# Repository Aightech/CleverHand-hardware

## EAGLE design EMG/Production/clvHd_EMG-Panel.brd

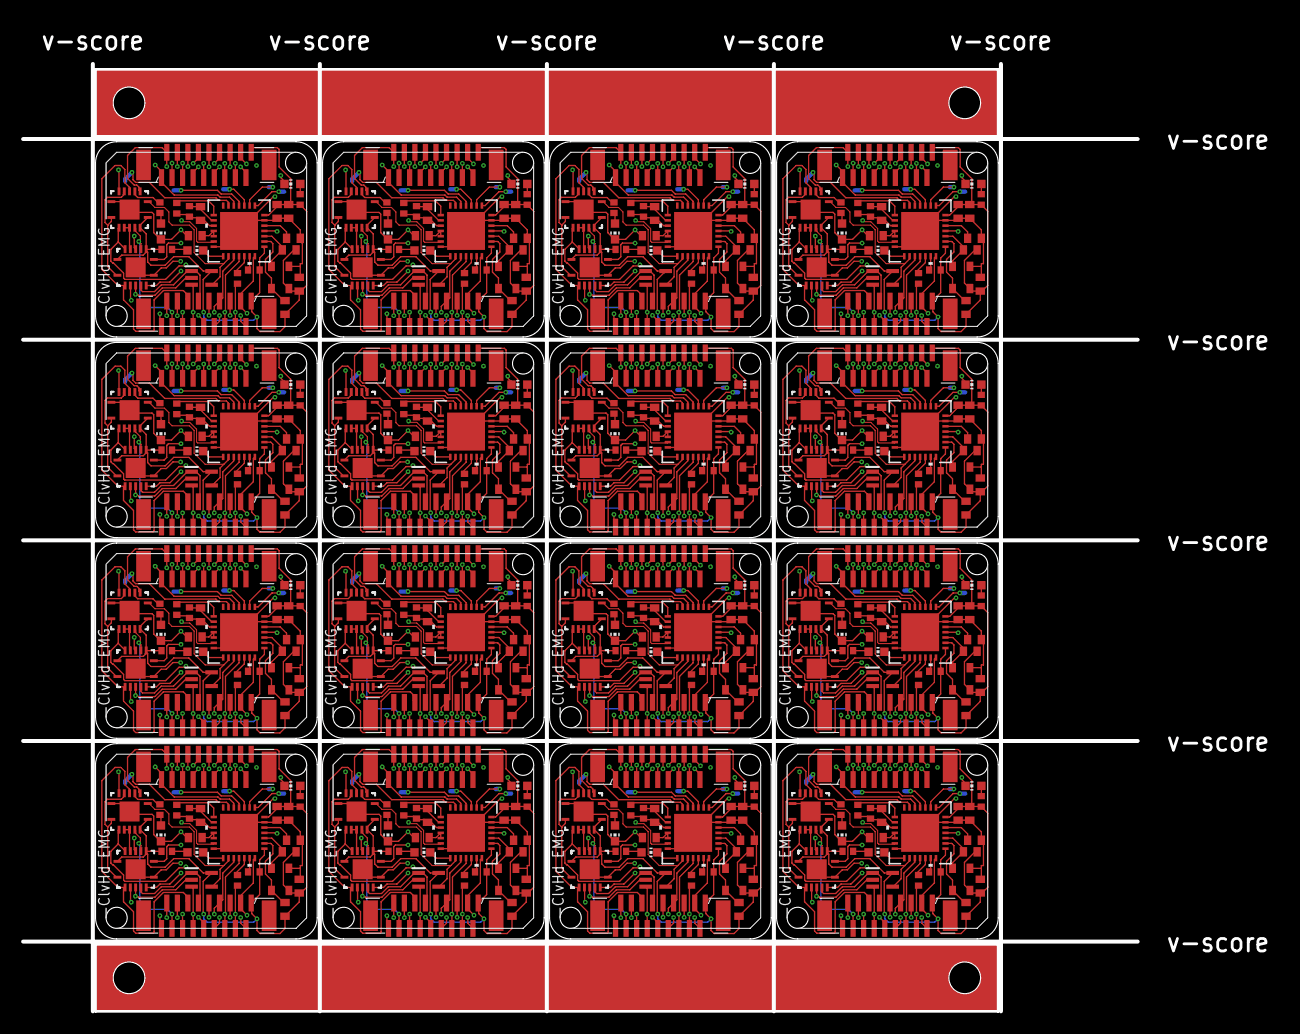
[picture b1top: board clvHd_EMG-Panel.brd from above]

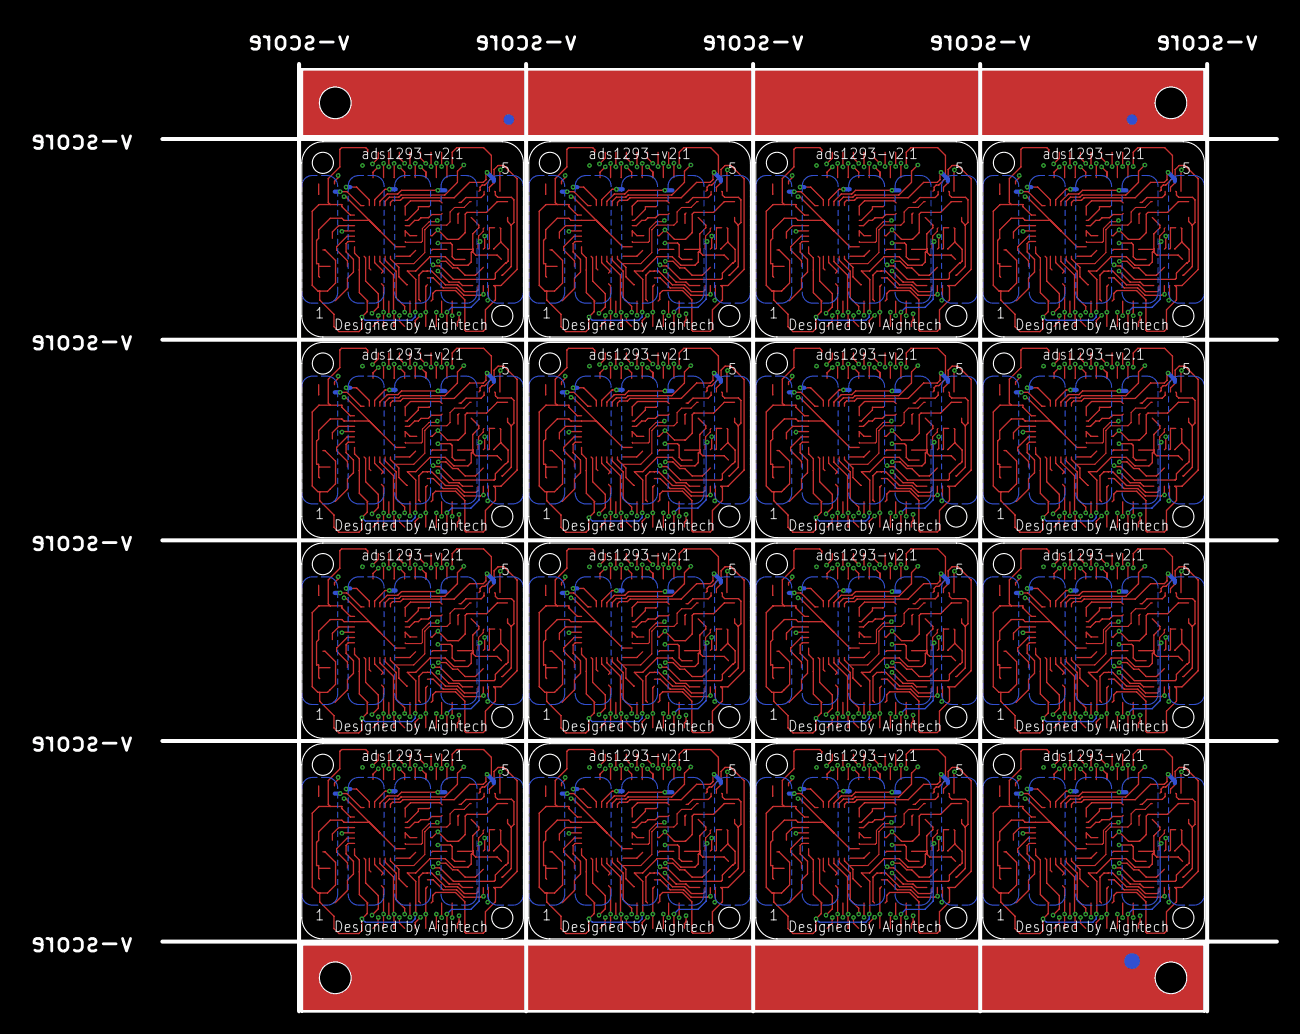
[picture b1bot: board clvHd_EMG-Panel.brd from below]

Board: 4 copper layers, 105.6 x 89.8 mm, 406 parts (3 on the bottom side), 576 nets.

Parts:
AND_IC, AND_IC1, AND_IC2, AND_IC3, AND_IC4, AND_IC5, AND_IC6, AND_IC7, AND_IC8, AND_IC9, AND_IC10, AND_IC11, AND_IC12, AND_IC13, AND_IC14, AND_IC15: SN74ALVC08LARGE; SN74LVC86ARGYR
C1, C2, C9, C10, C14, C15, C25, C26, C33, C34, C41, C42, C49, C50, C57, C58, C65, C66, C73, C74, C81, C82, C89, C90, C97, C98, C105, C106, C113, C114, C121, C122: 22pF; C0402
C3, C4, C6, C7, C12, C13, C16, C17, C18, C19, C22, C23, C27, C28, C30, C31, C35, C36, C38, C39, C43, C44, C46, C47, C51, C52, C54, C55, C59, C60, C62, C63, C67, C68, C70, C71, C75, C76, C78, C79, C83, C84, C86, C87, C91, C92, C94, C95, C99, C100, C102, C103, C107, C108, C110, C111, C115, C116, C118, C119, C123, C124, C126, C127: 100nF; C0402
C5, C11, C21, C29, C37, C45, C53, C61, C69, C77, C85, C93, C101, C109, C117, C125: 1nF; C0402
C8, C20, C24, C32, C40, C48, C56, C64, C72, C80, C88, C96, C104, C112, C120, C128: 1uF; C0402
E$1, E$2, E$3, E$4: FIDUCIAL-1X2
E$5, E$6: FIDUCIAL-1.5X3
J1, J2, J3, J4, J5, J6, J7, J8, J9, J10, J11, J12, J13, J14, J15, J16, J17, J18, J19, J20, J21, J22, J23, J24, J25, J26, J27, J28, J29, J30, J31, J32: XF2J-1824-12
L1, L2, L3, L4, L5, L6, L7, L8, L9, L10, L11, L12, L13, L14, L15, L16, L17, L18, L19, L20, L21, L22, L23, L24, L25, L26, L27, L28, L29, L30, L31, L32, L33, L34, L35, L36, L37, L38, L39, L40, L41, L42, L43, L44, L45, L46, L47, L48: LED 0603; CHIP-LED0603
NAND_IC, NAND_IC1, NAND_IC2, NAND_IC3, NAND_IC4, NAND_IC5, NAND_IC6, NAND_IC7, NAND_IC8, NAND_IC9, NAND_IC10, NAND_IC11, NAND_IC12, NAND_IC13, NAND_IC14, NAND_IC15: SN74LVC1G132DCKT; SOT65P210X110-5N
R1, R3, R7, R8, R9, R12, R16, R20, R21, R23, R27, R28, R30, R34, R35, R37, R41, R42, R44, R48, R49, R51, R55, R56, R58, R62, R63, R65, R69, R70, R72, R76, R77, R79, R83, R84, R86, R90, R91, R93, R97, R98, R100, R104, R105, R107, R111, R112: 100; R0402
R2, R10, R11, R22, R29, R36, R43, R50, R57, R64, R71, R78, R85, R92, R99, R106: 51; R0402
R4, R13, R17, R24, R31, R38, R45, R52, R59, R66, R73, R80, R87, R94, R101, R108: 1M; R0402
R5, R14, R18, R25, R32, R39, R46, R53, R60, R67, R74, R81, R88, R95, R102, R109: 10k; R0402
R6, R15, R19, R26, R33, R40, R47, R54, R61, R68, R75, R82, R89, R96, R103, R110: 10M; R0402
U1, U2, U3, U4, U5, U6, U7, U8, U9, U10, U11, U12, U13, U14, U15, U16: ADS1293CISQ/NOPB; RSG28_3P6X3P6_TEX
U$1, U$2, U$3, U$4, U$5, U$6, U$7, U$8, U$9, U$10, U$11, U$12, U$13, U$14, U$15, U$16: C387328; SMD-3225_4P
XOR_IC, XOR_IC1, XOR_IC2, XOR_IC3, XOR_IC4, XOR_IC5, XOR_IC6, XOR_IC7, XOR_IC8, XOR_IC9, XOR_IC10, XOR_IC11, XOR_IC12, XOR_IC13, XOR_IC14, XOR_IC15: SN74LVC86A; SN74LVC86ARGYR

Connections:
A0: AND_IC.12, J1.16, XOR_IC.10
A1: AND_IC.9, J1.14, XOR_IC.13
A2: AND_IC.4, J1.13, XOR_IC.2
A3: J1.11, NAND_IC.1, XOR_IC.5
A4: AND_IC1.9, J3.14, XOR_IC1.13
A5: AND_IC1.4, J3.13, XOR_IC1.2
A6: J3.11, NAND_IC1.1, XOR_IC1.5
A7: AND_IC1.12, J3.16, XOR_IC1.10
A8: AND_IC2.9, J5.14, XOR_IC2.13
A9: AND_IC2.4, J5.13, XOR_IC2.2
A10: J5.11, NAND_IC2.1, XOR_IC2.5
A11: AND_IC2.12, J5.16, XOR_IC2.10
A12: AND_IC3.9, J7.14, XOR_IC3.13
A13: AND_IC3.4, J7.13, XOR_IC3.2
A14: J7.11, NAND_IC3.1, XOR_IC3.5
A15: AND_IC3.12, J7.16, XOR_IC3.10
A16: AND_IC4.9, J9.14, XOR_IC4.13
A17: AND_IC4.4, J9.13, XOR_IC4.2
A18: J9.11, NAND_IC4.1, XOR_IC4.5
A19: AND_IC4.12, J9.16, XOR_IC4.10
A20: AND_IC5.9, J11.14, XOR_IC5.13
A21: AND_IC5.4, J11.13, XOR_IC5.2
A22: J11.11, NAND_IC5.1, XOR_IC5.5
A23: AND_IC5.12, J11.16, XOR_IC5.10
A24: AND_IC6.9, J13.14, XOR_IC6.13
A25: AND_IC6.4, J13.13, XOR_IC6.2
A26: J13.11, NAND_IC6.1, XOR_IC6.5
A27: AND_IC6.12, J13.16, XOR_IC6.10
A28: AND_IC7.9, J15.14, XOR_IC7.13
A29: AND_IC7.4, J15.13, XOR_IC7.2
A30: J15.11, NAND_IC7.1, XOR_IC7.5
A31: AND_IC7.12, J15.16, XOR_IC7.10
A32: AND_IC8.9, J17.14, XOR_IC8.13
A33: AND_IC8.4, J17.13, XOR_IC8.2
A34: J17.11, NAND_IC8.1, XOR_IC8.5
A35: AND_IC8.12, J17.16, XOR_IC8.10
A36: AND_IC9.9, J19.14, XOR_IC9.13
A37: AND_IC9.4, J19.13, XOR_IC9.2
A38: J19.11, NAND_IC9.1, XOR_IC9.5
A39: AND_IC9.12, J19.16, XOR_IC9.10
A40: AND_IC10.9, J21.14, XOR_IC10.13
A41: AND_IC10.4, J21.13, XOR_IC10.2
A42: J21.11, NAND_IC10.1, XOR_IC10.5
A43: AND_IC10.12, J21.16, XOR_IC10.10
A44: AND_IC11.9, J23.14, XOR_IC11.13
A45: AND_IC11.4, J23.13, XOR_IC11.2
A46: J23.11, NAND_IC11.1, XOR_IC11.5
A47: AND_IC11.12, J23.16, XOR_IC11.10
A48: AND_IC12.9, J25.14, XOR_IC12.13
A49: AND_IC12.4, J25.13, XOR_IC12.2
A50: J25.11, NAND_IC12.1, XOR_IC12.5
A51: AND_IC12.12, J25.16, XOR_IC12.10
A52: AND_IC13.9, J27.14, XOR_IC13.13
A53: AND_IC13.4, J27.13, XOR_IC13.2
A54: J27.11, NAND_IC13.1, XOR_IC13.5
A55: AND_IC13.12, J27.16, XOR_IC13.10
A56: AND_IC14.9, J29.14, XOR_IC14.13
A57: AND_IC14.4, J29.13, XOR_IC14.2
A58: J29.11, NAND_IC14.1, XOR_IC14.5
A59: AND_IC14.12, J29.16, XOR_IC14.10
A60: AND_IC15.9, J31.14, XOR_IC15.13
A61: AND_IC15.4, J31.13, XOR_IC15.2
A62: J31.11, NAND_IC15.1, XOR_IC15.5
A63: AND_IC15.12, J31.16, XOR_IC15.10
ALARMB: L2.C, U1.15
ALARMB1: L4.C, U2.15
ALARMB2: L7.C, U3.15
ALARMB3: L10.C, U4.15
ALARMB4: L13.C, U5.15
ALARMB5: L16.C, U6.15
ALARMB6: L19.C, U7.15
ALARMB7: L22.C, U8.15
ALARMB8: L25.C, U9.15
ALARMB9: L28.C, U10.15
ALARMB10: L31.C, U11.15
ALARMB11: L34.C, U12.15
ALARMB12: L37.C, U13.15
ALARMB13: L40.C, U14.15
ALARMB14: L43.C, U15.15
ALARMB15: L46.C, U16.15
CLK: J1.3, J2.16, U1.21
CLK1: J3.3, J4.16, U2.21
CLK2: J5.3, J6.16, U3.21
CLK3: J7.3, J8.16, U4.21
CLK4: J9.3, J10.16, U5.21
CLK5: J11.3, J12.16, U6.21
CLK6: J13.3, J14.16, U7.21
CLK7: J15.3, J16.16, U8.21
CLK8: J17.3, J18.16, U9.21
CLK9: J19.3, J20.16, U10.21
CLK10: J21.3, J22.16, U11.21
CLK11: J23.3, J24.16, U12.21
CLK12: J25.3, J26.16, U13.21
CLK13: J27.3, J28.16, U14.21
CLK14: J29.3, J30.16, U15.21
CLK15: J31.3, J32.16, U16.21
CMOUT: R14.1, U1.8
CMOUT1: R5.1, U2.8
CMOUT2: R18.1, U3.8
CMOUT3: R25.1, U4.8
CMOUT4: R32.1, U5.8
CMOUT5: R39.1, U6.8
CMOUT6: R46.1, U7.8
CMOUT7: R53.1, U8.8
CMOUT8: R60.1, U9.8
CMOUT9: R67.1, U10.8
CMOUT10: R74.1, U11.8
CMOUT11: R81.1, U12.8
CMOUT12: R88.1, U13.8
CMOUT13: R95.1, U14.8
CMOUT14: R102.1, U15.8
CMOUT15: R109.1, U16.8
CS: AND_IC.1, NAND_IC.4, U1.16
CS1: AND_IC1.1, NAND_IC1.4, U2.16
CS2: AND_IC2.1, NAND_IC2.4, U3.16
CS3: AND_IC3.1, NAND_IC3.4, U4.16
CS4: AND_IC4.1, NAND_IC4.4, U5.16
CS5: AND_IC5.1, NAND_IC5.4, U6.16
CS6: AND_IC6.1, NAND_IC6.4, U7.16
CS7: AND_IC7.1, NAND_IC7.4, U8.16
CS8: AND_IC8.1, NAND_IC8.4, U9.16
CS9: AND_IC9.1, NAND_IC9.4, U10.16
CS10: AND_IC10.1, NAND_IC10.4, U11.16
CS11: AND_IC11.1, NAND_IC11.4, U12.16
CS12: AND_IC12.1, NAND_IC12.4, U13.16
CS13: AND_IC13.1, NAND_IC13.4, U14.16
CS14: AND_IC14.1, NAND_IC14.4, U15.16
CS15: AND_IC15.1, NAND_IC15.4, U16.16
DIN: J1.6, J2.13, U1.18
DIN1: J3.6, J4.13, U2.18
DIN2: J5.6, J6.13, U3.18
DIN3: J7.6, J8.13, U4.18
DIN4: J9.6, J10.13, U5.18
DIN5: J11.6, J12.13, U6.18
DIN6: J13.6, J14.13, U7.18
DIN7: J15.6, J16.13, U8.18
DIN8: J17.6, J18.13, U9.18
DIN9: J19.6, J20.13, U10.18
DIN10: J21.6, J22.13, U11.18
DIN11: J23.6, J24.13, U12.18
DIN12: J25.6, J26.13, U13.18
DIN13: J27.6, J28.13, U14.18
DIN14: J29.6, J30.13, U15.18
DIN15: J31.6, J32.13, U16.18
DOUT: J1.4, J2.15, R10.2
DOUT1: J3.4, J4.15, R2.2
DOUT2: J5.4, J6.15, R11.2
DOUT3: J7.4, J8.15, R22.2
DOUT4: J9.4, J10.15, R29.2
DOUT5: J11.4, J12.15, R36.2
DOUT6: J13.4, J14.15, R43.2
DOUT7: J15.4, J16.15, R50.2
DOUT8: J17.4, J18.15, R57.2
DOUT9: J19.4, J20.15, R64.2
DOUT10: J21.4, J22.15, R71.2
DOUT11: J23.4, J24.15, R78.2
DOUT12: J25.4, J26.15, R85.2
DOUT13: J27.4, J28.15, R92.2
DOUT14: J29.4, J30.15, R99.2
DOUT15: J31.4, J32.15, R106.2
DRDYB: R13.1, U1.20
DRDYB1: R4.1, U2.20
DRDYB2: R17.1, U3.20
DRDYB3: R24.1, U4.20
DRDYB4: R31.1, U5.20
DRDYB5: R38.1, U6.20
DRDYB6: R45.1, U7.20
DRDYB7: R52.1, U8.20
DRDYB8: R59.1, U9.20
DRDYB9: R66.1, U10.20
DRDYB10: R73.1, U11.20
DRDYB11: R80.1, U12.20
DRDYB12: R87.1, U13.20
DRDYB13: R94.1, U14.20
DRDYB14: R101.1, U15.20
DRDYB15: R108.1, U16.20
GND: AND_IC.7, AND_IC.15, C12.2, C13.2, C16.2, C19.2, C20.2, J1.2, J1.5, J1.8, J1.12, J1.15, J2.4, J2.7, J2.11, J2.14, J2.17, L1.C, L3.C, NAND_IC.3, U1.14, U1.27, U1.29, U$1.2, XOR_IC.7, XOR_IC.15
GND1: AND_IC1.7, AND_IC1.15, C3.2, C4.2, C6.2, C7.2, C8.2, J3.2, J3.5, J3.8, J3.12, J3.15, J4.4, J4.7, J4.11, J4.14, J4.17, L5.C, L6.C, NAND_IC1.3, U2.14, U2.27, U2.29, U$2.2, XOR_IC1.7, XOR_IC1.15
GND2: AND_IC2.7, AND_IC2.15, C17.2, C18.2, C22.2, C23.2, C24.2, J5.2, J5.5, J5.8, J5.12, J5.15, J6.4, J6.7, J6.11, J6.14, J6.17, L8.C, L9.C, NAND_IC2.3, U3.14, U3.27, U3.29, U$3.2, XOR_IC2.7, XOR_IC2.15
GND3: AND_IC3.7, AND_IC3.15, C27.2, C28.2, C30.2, C31.2, C32.2, J7.2, J7.5, J7.8, J7.12, J7.15, J8.4, J8.7, J8.11, J8.14, J8.17, L11.C, L12.C, NAND_IC3.3, U4.14, U4.27, U4.29, U$4.2, XOR_IC3.7, XOR_IC3.15
GND4: AND_IC4.7, AND_IC4.15, C35.2, C36.2, C38.2, C39.2, C40.2, J9.2, J9.5, J9.8, J9.12, J9.15, J10.4, J10.7, J10.11, J10.14, J10.17, L14.C, L15.C, NAND_IC4.3, U5.14, U5.27, U5.29, U$5.2, XOR_IC4.7, XOR_IC4.15
GND5: AND_IC5.7, AND_IC5.15, C43.2, C44.2, C46.2, C47.2, C48.2, J11.2, J11.5, J11.8, J11.12, J11.15, J12.4, J12.7, J12.11, J12.14, J12.17, L17.C, L18.C, NAND_IC5.3, U6.14, U6.27, U6.29, U$6.2, XOR_IC5.7, XOR_IC5.15
GND6: AND_IC6.7, AND_IC6.15, C51.2, C52.2, C54.2, C55.2, C56.2, J13.2, J13.5, J13.8, J13.12, J13.15, J14.4, J14.7, J14.11, J14.14, J14.17, L20.C, L21.C, NAND_IC6.3, U7.14, U7.27, U7.29, U$7.2, XOR_IC6.7, XOR_IC6.15
GND7: AND_IC7.7, AND_IC7.15, C59.2, C60.2, C62.2, C63.2, C64.2, J15.2, J15.5, J15.8, J15.12, J15.15, J16.4, J16.7, J16.11, J16.14, J16.17, L23.C, L24.C, NAND_IC7.3, U8.14, U8.27, U8.29, U$8.2, XOR_IC7.7, XOR_IC7.15
GND8: AND_IC8.7, AND_IC8.15, C67.2, C68.2, C70.2, C71.2, C72.2, J17.2, J17.5, J17.8, J17.12, J17.15, J18.4, J18.7, J18.11, J18.14, J18.17, L26.C, L27.C, NAND_IC8.3, U9.14, U9.27, U9.29, U$9.2, XOR_IC8.7, XOR_IC8.15
GND9: AND_IC9.7, AND_IC9.15, C75.2, C76.2, C78.2, C79.2, C80.2, J19.2, J19.5, J19.8, J19.12, J19.15, J20.4, J20.7, J20.11, J20.14, J20.17, L29.C, L30.C, NAND_IC9.3, U10.14, U10.27, U10.29, U$10.2, XOR_IC9.7, XOR_IC9.15
GND10: AND_IC10.7, AND_IC10.15, C83.2, C84.2, C86.2, C87.2, C88.2, J21.2, J21.5, J21.8, J21.12, J21.15, J22.4, J22.7, J22.11, J22.14, J22.17, L32.C, L33.C, NAND_IC10.3, U11.14, U11.27, U11.29, U$11.2, XOR_IC10.7, XOR_IC10.15
GND11: AND_IC11.7, AND_IC11.15, C91.2, C92.2, C94.2, C95.2, C96.2, J23.2, J23.5, J23.8, J23.12, J23.15, J24.4, J24.7, J24.11, J24.14, J24.17, L35.C, L36.C, NAND_IC11.3, U12.14, U12.27, U12.29, U$12.2, XOR_IC11.7, XOR_IC11.15
GND12: AND_IC12.7, AND_IC12.15, C99.2, C100.2, C102.2, C103.2, C104.2, J25.2, J25.5, J25.8, J25.12, J25.15, J26.4, J26.7, J26.11, J26.14, J26.17, L38.C, L39.C, NAND_IC12.3, U13.14, U13.27, U13.29, U$13.2, XOR_IC12.7, XOR_IC12.15
GND13: AND_IC13.7, AND_IC13.15, C107.2, C108.2, C110.2, C111.2, C112.2, J27.2, J27.5, J27.8, J27.12, J27.15, J28.4, J28.7, J28.11, J28.14, J28.17, L41.C, L42.C, NAND_IC13.3, U14.14, U14.27, U14.29, U$14.2, XOR_IC13.7, XOR_IC13.15
GND14: AND_IC14.7, AND_IC14.15, C115.2, C116.2, C118.2, C119.2, C120.2, J29.2, J29.5, J29.8, J29.12, J29.15, J30.4, J30.7, J30.11, J30.14, J30.17, L44.C, L45.C, NAND_IC14.3, U15.14, U15.27, U15.29, U$15.2, XOR_IC14.7, XOR_IC14.15
GND15: AND_IC15.7, AND_IC15.15, C123.2, C124.2, C126.2, C127.2, C128.2, J31.2, J31.5, J31.8, J31.12, J31.15, J32.4, J32.7, J32.11, J32.14, J32.17, L47.C, L48.C, NAND_IC15.3, U16.14, U16.27, U16.29, U$16.2, XOR_IC15.7, XOR_IC15.15
GPIO1: AND_IC.2, J1.17, J2.2
GPIO2: AND_IC1.2, J3.17, J4.2
GPIO3: AND_IC2.2, J5.17, J6.2
GPIO4: AND_IC3.2, J7.17, J8.2
GPIO5: AND_IC4.2, J9.17, J10.2
GPIO6: AND_IC5.2, J11.17, J12.2
GPIO7: AND_IC6.2, J13.17, J14.2
GPIO8: AND_IC7.2, J15.17, J16.2
GPIO9: AND_IC8.2, J17.17, J18.2
GPIO10: AND_IC9.2, J19.17, J20.2
GPIO11: AND_IC10.2, J21.17, J22.2
GPIO12: AND_IC11.2, J23.17, J24.2
GPIO13: AND_IC12.2, J25.17, J26.2
GPIO14: AND_IC13.2, J27.17, J28.2
GPIO15: AND_IC14.2, J29.17, J30.2
GPIO16: AND_IC15.2, J31.17, J32.2
IN5: J1.18, J2.1, U1.5
IN10: J3.18, J4.1, U2.5
IN16: J5.18, J6.1, U3.5
IN22: J7.18, J8.1, U4.5
IN28: J9.18, J10.1, U5.5
IN34: J11.18, J12.1, U6.5
IN40: J13.18, J14.1, U7.5
IN46: J15.18, J16.1, U8.5
IN52: J17.18, J18.1, U9.5
IN58: J19.18, J20.1, U10.5
IN64: J21.18, J22.1, U11.5
IN70: J23.18, J24.1, U12.5
IN76: J25.18, J26.1, U13.5
IN82: J27.18, J28.1, U14.5
IN88: J29.18, J30.1, U15.5
IN94: J31.18, J32.1, U16.5
unnamed: R2.1, U2.19
unnamed: L1.A, R7.2
unnamed: R10.1, U1.19
unnamed: C10.2, U1.23, U$1.4
unnamed: AND_IC.3, R1.2
unnamed: L2.A, R12.1
unnamed: L3.A, R1.1
unnamed: C9.2, U1.24, U$1.3
unnamed: C20.1, U1.26
unnamed: C2.2, U2.23, U$2.4
unnamed: AND_IC.10, AND_IC.11, XOR_IC.12
unnamed: C1.2, U2.24, U$2.3
unnamed: AND_IC.5, AND_IC.8, XOR_IC.1
unnamed: C5.1, R5.2, R6.2, U2.10
unnamed: C11.1, R14.2, R15.2, U1.10
unnamed: AND_IC.6, NAND_IC.2, XOR_IC.4
unnamed: C8.1, U2.26
unnamed: L5.A, R8.2
unnamed: L4.A, R3.1
unnamed: AND_IC1.3, R9.2
unnamed: L6.A, R9.1
unnamed: AND_IC1.6, NAND_IC1.2, XOR_IC1.4
unnamed: AND_IC1.5, AND_IC1.8, XOR_IC1.1
unnamed: AND_IC1.10, AND_IC1.11, XOR_IC1.12
unnamed: R11.1, U3.19
unnamed: C15.2, U3.23, U$3.4
unnamed: C14.2, U3.24, U$3.3
unnamed: C21.1, R18.2, R19.2, U3.10
unnamed: C24.1, U3.26
unnamed: L8.A, R20.2
unnamed: L7.A, R16.1
unnamed: AND_IC2.3, R21.2
unnamed: L9.A, R21.1
unnamed: AND_IC2.6, NAND_IC2.2, XOR_IC2.4
unnamed: AND_IC2.5, AND_IC2.8, XOR_IC2.1
unnamed: AND_IC2.10, AND_IC2.11, XOR_IC2.12
unnamed: R22.1, U4.19
unnamed: C26.2, U4.23, U$4.4
unnamed: C25.2, U4.24, U$4.3
unnamed: C29.1, R25.2, R26.2, U4.10
unnamed: C32.1, U4.26
unnamed: L11.A, R27.2
unnamed: L10.A, R23.1
unnamed: AND_IC3.3, R28.2
unnamed: L12.A, R28.1
unnamed: AND_IC3.6, NAND_IC3.2, XOR_IC3.4
unnamed: AND_IC3.5, AND_IC3.8, XOR_IC3.1
unnamed: AND_IC3.10, AND_IC3.11, XOR_IC3.12
unnamed: R29.1, U5.19
unnamed: C34.2, U5.23, U$5.4
unnamed: C33.2, U5.24, U$5.3
unnamed: C37.1, R32.2, R33.2, U5.10
unnamed: C40.1, U5.26
unnamed: L14.A, R34.2
unnamed: L13.A, R30.1
unnamed: AND_IC4.3, R35.2
unnamed: L15.A, R35.1
unnamed: AND_IC4.6, NAND_IC4.2, XOR_IC4.4
unnamed: AND_IC4.5, AND_IC4.8, XOR_IC4.1
unnamed: AND_IC4.10, AND_IC4.11, XOR_IC4.12
unnamed: R36.1, U6.19
unnamed: C42.2, U6.23, U$6.4
unnamed: C41.2, U6.24, U$6.3
unnamed: C45.1, R39.2, R40.2, U6.10
unnamed: C48.1, U6.26
unnamed: L17.A, R41.2
unnamed: L16.A, R37.1
unnamed: AND_IC5.3, R42.2
unnamed: L18.A, R42.1
unnamed: AND_IC5.6, NAND_IC5.2, XOR_IC5.4
unnamed: AND_IC5.5, AND_IC5.8, XOR_IC5.1
unnamed: AND_IC5.10, AND_IC5.11, XOR_IC5.12
unnamed: R43.1, U7.19
unnamed: C50.2, U7.23, U$7.4
unnamed: C49.2, U7.24, U$7.3
unnamed: C53.1, R46.2, R47.2, U7.10
unnamed: C56.1, U7.26
unnamed: L20.A, R48.2
unnamed: L19.A, R44.1
unnamed: AND_IC6.3, R49.2
unnamed: L21.A, R49.1
unnamed: AND_IC6.6, NAND_IC6.2, XOR_IC6.4
unnamed: AND_IC6.5, AND_IC6.8, XOR_IC6.1
unnamed: AND_IC6.10, AND_IC6.11, XOR_IC6.12
unnamed: R50.1, U8.19
unnamed: C58.2, U8.23, U$8.4
unnamed: C57.2, U8.24, U$8.3
unnamed: C61.1, R53.2, R54.2, U8.10
unnamed: C64.1, U8.26
unnamed: L23.A, R55.2
unnamed: L22.A, R51.1
unnamed: AND_IC7.3, R56.2
unnamed: L24.A, R56.1
unnamed: AND_IC7.6, NAND_IC7.2, XOR_IC7.4
unnamed: AND_IC7.5, AND_IC7.8, XOR_IC7.1
unnamed: AND_IC7.10, AND_IC7.11, XOR_IC7.12
unnamed: R57.1, U9.19
unnamed: C66.2, U9.23, U$9.4
unnamed: C65.2, U9.24, U$9.3
unnamed: C69.1, R60.2, R61.2, U9.10
unnamed: C72.1, U9.26
unnamed: L26.A, R62.2
unnamed: L25.A, R58.1
unnamed: AND_IC8.3, R63.2
unnamed: L27.A, R63.1
unnamed: AND_IC8.6, NAND_IC8.2, XOR_IC8.4
unnamed: AND_IC8.5, AND_IC8.8, XOR_IC8.1
unnamed: AND_IC8.10, AND_IC8.11, XOR_IC8.12
unnamed: R64.1, U10.19
unnamed: C74.2, U10.23, U$10.4
unnamed: C73.2, U10.24, U$10.3
unnamed: C77.1, R67.2, R68.2, U10.10
unnamed: C80.1, U10.26
unnamed: L29.A, R69.2
unnamed: L28.A, R65.1
unnamed: AND_IC9.3, R70.2
unnamed: L30.A, R70.1
unnamed: AND_IC9.6, NAND_IC9.2, XOR_IC9.4
unnamed: AND_IC9.5, AND_IC9.8, XOR_IC9.1
unnamed: AND_IC9.10, AND_IC9.11, XOR_IC9.12
unnamed: R71.1, U11.19
unnamed: C82.2, U11.23, U$11.4
unnamed: C81.2, U11.24, U$11.3
unnamed: C85.1, R74.2, R75.2, U11.10
unnamed: C88.1, U11.26
unnamed: L32.A, R76.2
unnamed: L31.A, R72.1
unnamed: AND_IC10.3, R77.2
unnamed: L33.A, R77.1
unnamed: AND_IC10.6, NAND_IC10.2, XOR_IC10.4
unnamed: AND_IC10.5, AND_IC10.8, XOR_IC10.1
unnamed: AND_IC10.10, AND_IC10.11, XOR_IC10.12
unnamed: R78.1, U12.19
unnamed: C90.2, U12.23, U$12.4
unnamed: C89.2, U12.24, U$12.3
unnamed: C93.1, R81.2, R82.2, U12.10
unnamed: C96.1, U12.26
unnamed: L35.A, R83.2
unnamed: L34.A, R79.1
unnamed: AND_IC11.3, R84.2
unnamed: L36.A, R84.1
unnamed: AND_IC11.6, NAND_IC11.2, XOR_IC11.4
unnamed: AND_IC11.5, AND_IC11.8, XOR_IC11.1
unnamed: AND_IC11.10, AND_IC11.11, XOR_IC11.12
unnamed: R85.1, U13.19
unnamed: C98.2, U13.23, U$13.4
unnamed: C97.2, U13.24, U$13.3
unnamed: C101.1, R88.2, R89.2, U13.10
unnamed: C104.1, U13.26
unnamed: L38.A, R90.2
unnamed: L37.A, R86.1
unnamed: AND_IC12.3, R91.2
unnamed: L39.A, R91.1
unnamed: AND_IC12.6, NAND_IC12.2, XOR_IC12.4
unnamed: AND_IC12.5, AND_IC12.8, XOR_IC12.1
unnamed: AND_IC12.10, AND_IC12.11, XOR_IC12.12
unnamed: R92.1, U14.19
unnamed: C106.2, U14.23, U$14.4
unnamed: C105.2, U14.24, U$14.3
unnamed: C109.1, R95.2, R96.2, U14.10
unnamed: C112.1, U14.26
unnamed: L41.A, R97.2
unnamed: L40.A, R93.1
unnamed: AND_IC13.3, R98.2
unnamed: L42.A, R98.1
unnamed: AND_IC13.6, NAND_IC13.2, XOR_IC13.4
unnamed: AND_IC13.5, AND_IC13.8, XOR_IC13.1
unnamed: AND_IC13.10, AND_IC13.11, XOR_IC13.12
unnamed: R99.1, U15.19
unnamed: C114.2, U15.23, U$15.4
unnamed: C113.2, U15.24, U$15.3
unnamed: C117.1, R102.2, R103.2, U15.10
unnamed: C120.1, U15.26
unnamed: L44.A, R104.2
unnamed: L43.A, R100.1
unnamed: AND_IC14.3, R105.2
unnamed: L45.A, R105.1
unnamed: AND_IC14.6, NAND_IC14.2, XOR_IC14.4
unnamed: AND_IC14.5, AND_IC14.8, XOR_IC14.1
unnamed: AND_IC14.10, AND_IC14.11, XOR_IC14.12
unnamed: R106.1, U16.19
unnamed: C122.2, U16.23, U$16.4
unnamed: C121.2, U16.24, U$16.3
unnamed: C125.1, R109.2, R110.2, U16.10
unnamed: C128.1, U16.26
unnamed: L47.A, R111.2
unnamed: L46.A, R107.1
unnamed: AND_IC15.3, R112.2
unnamed: L48.A, R112.1
unnamed: AND_IC15.6, NAND_IC15.2, XOR_IC15.4
unnamed: AND_IC15.5, AND_IC15.8, XOR_IC15.1
unnamed: AND_IC15.10, AND_IC15.11, XOR_IC15.12
RLDOUT: C11.2, R15.1, U1.9
RLDOUT1: C5.2, R6.1, U2.9
RLDOUT2: C21.2, R19.1, U3.9
RLDOUT3: C29.2, R26.1, U4.9
RLDOUT4: C37.2, R33.1, U5.9
RLDOUT5: C45.2, R40.1, U6.9
RLDOUT6: C53.2, R47.1, U7.9
RLDOUT7: C61.2, R54.1, U8.9
RLDOUT8: C69.2, R61.1, U9.9
RLDOUT9: C77.2, R68.1, U10.9
RLDOUT10: C85.2, R75.1, U11.9
RLDOUT11: C93.2, R82.1, U12.9
RLDOUT12: C101.2, R89.1, U13.9
RLDOUT13: C109.2, R96.1, U14.9
RLDOUT14: C117.2, R103.1, U15.9
RLDOUT15: C125.2, R110.1, U16.9
RLDREF: C12.1, U1.11, U1.12
RLDREF1: C3.1, U2.11, U2.12
RLDREF2: C17.1, U3.11, U3.12
RLDREF3: C27.1, U4.11, U4.12
RLDREF4: C35.1, U5.11, U5.12
RLDREF5: C43.1, U6.11, U6.12
RLDREF6: C51.1, U7.11, U7.12
RLDREF7: C59.1, U8.11, U8.12
RLDREF8: C67.1, U9.11, U9.12
RLDREF9: C75.1, U10.11, U10.12
RLDREF10: C83.1, U11.11, U11.12
RLDREF11: C91.1, U12.11, U12.12
RLDREF12: C99.1, U13.11, U13.12
RLDREF13: C107.1, U14.11, U14.12
RLDREF14: C115.1, U15.11, U15.12
RLDREF15: C123.1, U16.11, U16.12
RST: J1.10, J2.9, U1.25
RST1: J3.10, J4.9, U2.25
RST2: J5.10, J6.9, U3.25
RST3: J7.10, J8.9, U4.25
RST4: J9.10, J10.9, U5.25
RST5: J11.10, J12.9, U6.25
RST6: J13.10, J14.9, U7.25
RST7: J15.10, J16.9, U8.25
RST8: J17.10, J18.9, U9.25
RST9: J19.10, J20.9, U10.25
RST10: J21.10, J22.9, U11.25
RST11: J23.10, J24.9, U12.25
RST12: J25.10, J26.9, U13.25
RST13: J27.10, J28.9, U14.25
RST14: J29.10, J30.9, U15.25
RST15: J31.10, J32.9, U16.25
S0: J2.3, XOR_IC.8
S1: J2.5, XOR_IC.11
S2: J2.6, XOR_IC.3
S3: J2.8, XOR_IC.6
S4: J4.3, XOR_IC1.8
S5: J4.5, XOR_IC1.11
S6: J4.6, XOR_IC1.3
S7: J4.8, XOR_IC1.6
S8: J6.3, XOR_IC2.8
S9: J6.5, XOR_IC2.11
S10: J6.6, XOR_IC2.3
S11: J6.8, XOR_IC2.6
S12: J8.3, XOR_IC3.8
S13: J8.5, XOR_IC3.11
S14: J8.6, XOR_IC3.3
S15: J8.8, XOR_IC3.6
S16: J10.3, XOR_IC4.8
S17: J10.5, XOR_IC4.11
S18: J10.6, XOR_IC4.3
S19: J10.8, XOR_IC4.6
S20: J12.3, XOR_IC5.8
S21: J12.5, XOR_IC5.11
S22: J12.6, XOR_IC5.3
S23: J12.8, XOR_IC5.6
S24: J14.3, XOR_IC6.8
S25: J14.5, XOR_IC6.11
S26: J14.6, XOR_IC6.3
S27: J14.8, XOR_IC6.6
S28: J16.3, XOR_IC7.8
S29: J16.5, XOR_IC7.11
S30: J16.6, XOR_IC7.3
S31: J16.8, XOR_IC7.6
S32: J18.3, XOR_IC8.8
S33: J18.5, XOR_IC8.11
S34: J18.6, XOR_IC8.3
S35: J18.8, XOR_IC8.6
S36: J20.3, XOR_IC9.8
S37: J20.5, XOR_IC9.11
S38: J20.6, XOR_IC9.3
S39: J20.8, XOR_IC9.6
S40: J22.3, XOR_IC10.8
S41: J22.5, XOR_IC10.11
S42: J22.6, XOR_IC10.3
S43: J22.8, XOR_IC10.6
S44: J24.3, XOR_IC11.8
S45: J24.5, XOR_IC11.11
S46: J24.6, XOR_IC11.3
S47: J24.8, XOR_IC11.6
S48: J26.3, XOR_IC12.8
S49: J26.5, XOR_IC12.11
S50: J26.6, XOR_IC12.3
S51: J26.8, XOR_IC12.6
S52: J28.3, XOR_IC13.8
S53: J28.5, XOR_IC13.11
S54: J28.6, XOR_IC13.3
S55: J28.8, XOR_IC13.6
S56: J30.3, XOR_IC14.8
S57: J30.5, XOR_IC14.11
S58: J30.6, XOR_IC14.3
S59: J30.8, XOR_IC14.6
S60: J32.3, XOR_IC15.8
S61: J32.5, XOR_IC15.11
S62: J32.6, XOR_IC15.3
S63: J32.8, XOR_IC15.6
SCLK: J1.7, J2.12, U1.17
SCLK1: J3.7, J4.12, U2.17
SCLK2: J5.7, J6.12, U3.17
SCLK3: J7.7, J8.12, U4.17
SCLK4: J9.7, J10.12, U5.17
SCLK5: J11.7, J12.12, U6.17
SCLK6: J13.7, J14.12, U7.17
SCLK7: J15.7, J16.12, U8.17
SCLK8: J17.7, J18.12, U9.17
SCLK9: J19.7, J20.12, U10.17
SCLK10: J21.7, J22.12, U11.17
SCLK11: J23.7, J24.12, U12.17
SCLK12: J25.7, J26.12, U13.17
SCLK13: J27.7, J28.12, U14.17
SCLK14: J29.7, J30.12, U15.17
SCLK15: J31.7, J32.12, U16.17
SYNCB: J1.9, J2.10, U1.13
SYNCB1: J3.9, J4.10, U2.13
SYNCB2: J5.9, J6.10, U3.13
SYNCB3: J7.9, J8.10, U4.13
SYNCB4: J9.9, J10.10, U5.13
SYNCB5: J11.9, J12.10, U6.13
SYNCB6: J13.9, J14.10, U7.13
SYNCB7: J15.9, J16.10, U8.13
SYNCB8: J17.9, J18.10, U9.13
SYNCB9: J19.9, J20.10, U10.13
SYNCB10: J21.9, J22.10, U11.13
SYNCB11: J23.9, J24.10, U12.13
SYNCB12: J25.9, J26.10, U13.13
SYNCB13: J27.9, J28.10, U14.13
SYNCB14: J29.9, J30.10, U15.13
SYNCB15: J31.9, J32.10, U16.13
VDD: AND_IC.13, AND_IC.14, C9.1, C10.1, C13.1, C16.1, C19.1, J1.1, J2.18, NAND_IC.5, R7.1, R12.2, R13.2, U1.22, U1.28, U$1.1, XOR_IC.9, XOR_IC.14
VDD1: AND_IC1.13, AND_IC1.14, C1.1, C2.1, C4.1, C6.1, C7.1, J3.1, J4.18, NAND_IC1.5, R3.2, R4.2, R8.1, U2.22, U2.28, U$2.1, XOR_IC1.9, XOR_IC1.14
VDD2: AND_IC2.13, AND_IC2.14, C14.1, C15.1, C18.1, C22.1, C23.1, J5.1, J6.18, NAND_IC2.5, R16.2, R17.2, R20.1, U3.22, U3.28, U$3.1, XOR_IC2.9, XOR_IC2.14
VDD3: AND_IC3.13, AND_IC3.14, C25.1, C26.1, C28.1, C30.1, C31.1, J7.1, J8.18, NAND_IC3.5, R23.2, R24.2, R27.1, U4.22, U4.28, U$4.1, XOR_IC3.9, XOR_IC3.14
VDD4: AND_IC4.13, AND_IC4.14, C33.1, C34.1, C36.1, C38.1, C39.1, J9.1, J10.18, NAND_IC4.5, R30.2, R31.2, R34.1, U5.22, U5.28, U$5.1, XOR_IC4.9, XOR_IC4.14
VDD5: AND_IC5.13, AND_IC5.14, C41.1, C42.1, C44.1, C46.1, C47.1, J11.1, J12.18, NAND_IC5.5, R37.2, R38.2, R41.1, U6.22, U6.28, U$6.1, XOR_IC5.9, XOR_IC5.14
VDD6: AND_IC6.13, AND_IC6.14, C49.1, C50.1, C52.1, C54.1, C55.1, J13.1, J14.18, NAND_IC6.5, R44.2, R45.2, R48.1, U7.22, U7.28, U$7.1, XOR_IC6.9, XOR_IC6.14
VDD7: AND_IC7.13, AND_IC7.14, C57.1, C58.1, C60.1, C62.1, C63.1, J15.1, J16.18, NAND_IC7.5, R51.2, R52.2, R55.1, U8.22, U8.28, U$8.1, XOR_IC7.9, XOR_IC7.14
VDD8: AND_IC8.13, AND_IC8.14, C65.1, C66.1, C68.1, C70.1, C71.1, J17.1, J18.18, NAND_IC8.5, R58.2, R59.2, R62.1, U9.22, U9.28, U$9.1, XOR_IC8.9, XOR_IC8.14
VDD9: AND_IC9.13, AND_IC9.14, C73.1, C74.1, C76.1, C78.1, C79.1, J19.1, J20.18, NAND_IC9.5, R65.2, R66.2, R69.1, U10.22, U10.28, U$10.1, XOR_IC9.9, XOR_IC9.14
VDD10: AND_IC10.13, AND_IC10.14, C81.1, C82.1, C84.1, C86.1, C87.1, J21.1, J22.18, NAND_IC10.5, R72.2, R73.2, R76.1, U11.22, U11.28, U$11.1, XOR_IC10.9, XOR_IC10.14
VDD11: AND_IC11.13, AND_IC11.14, C89.1, C90.1, C92.1, C94.1, C95.1, J23.1, J24.18, NAND_IC11.5, R79.2, R80.2, R83.1, U12.22, U12.28, U$12.1, XOR_IC11.9, XOR_IC11.14
VDD12: AND_IC12.13, AND_IC12.14, C97.1, C98.1, C100.1, C102.1, C103.1, J25.1, J26.18, NAND_IC12.5, R86.2, R87.2, R90.1, U13.22, U13.28, U$13.1, XOR_IC12.9, XOR_IC12.14
VDD13: AND_IC13.13, AND_IC13.14, C105.1, C106.1, C108.1, C110.1, C111.1, J27.1, J28.18, NAND_IC13.5, R93.2, R94.2, R97.1, U14.22, U14.28, U$14.1, XOR_IC13.9, XOR_IC13.14
VDD14: AND_IC14.13, AND_IC14.14, C113.1, C114.1, C116.1, C118.1, C119.1, J29.1, J30.18, NAND_IC14.5, R100.2, R101.2, R104.1, U15.22, U15.28, U$15.1, XOR_IC14.9, XOR_IC14.14
VDD15: AND_IC15.13, AND_IC15.14, C121.1, C122.1, C124.1, C126.1, C127.1, J31.1, J32.18, NAND_IC15.5, R107.2, R108.2, R111.1, U16.22, U16.28, U$16.1, XOR_IC15.9, XOR_IC15.14

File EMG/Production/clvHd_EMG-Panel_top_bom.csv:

Comment,Designator,Footprint,LCSC Part #
1M,E$1 E$3 E$5 R4 R13 R17 R24 R31 R38 R45 R52 R59 R66 R73 R80 R87 R94 R101 R108,R0402,
1nF,C5 C11 C21 C29 C37 C45 C53 C61 C69 C77 C85 C93 C101 C109 C117 C125,C0402,
1uF,C8 C20 C24 C32 C40 C48 C56 C64 C72 C80 C88 C96 C104 C112 C120 C128,C0402,
10M,R6 R15 R19 R26 R33 R40 R47 R54 R61 R68 R75 R82 R89 R96 R103 R110,R0402,
10k,R5 R14 R18 R25 R32 R39 R46 R53 R60 R67 R74 R81 R88 R95 R102 R109,R0402,
22pF,C1 C2 C9 C10 C14 C15 C25 C26 C33 C34 C41 C42 C49 C50 C57 C58 C65 C66 C73 C74 C81 C82 C89 C90 C97 C98 C105 C106 C113 C114 C121 C122,C0402,
51,R2 R10 R11 R22 R29 R36 R43 R50 R57 R64 R71 R78 R85 R92 R99 R106,R0402,
100,R1 R3 R7 R8 R9 R12 R16 R20 R21 R23 R27 R28 R30 R34 R35 R37 R41 R42 R44 R48 R49 R51 R55 R56 R58 R62 R63 R65 R69 R70 R72 R76 R77 R79 R83 R84 R86 R90 R91 R93 R97 R98 R100 R104 R105 R107 R111 R112,R0402,
100nF,C3 C4 C6 C7 C12 C13 C16 C17 C18 C19 C22 C23 C27 C28 C30 C31 C35 C36 C38 C39 C43 C44 C46 C47 C51 C52 C54 C55 C59 C60 C62 C63 C67 C68 C70 C71 C75 C76 C78 C79 C83 C84 C86 C87 C91 C92 C94 C95 C99 C100 C102 C103 C107 C108 C110 C111 C115 C116 C118 C119 C123 C124 C126 C127,C0402,
ADS1293CISQ/NOPB,U1 U2 U3 U4 U5 U6 U7 U8 U9 U10 U11 U12 U13 U14 U15 U16,RSG28_3P6X3P6_TEX,
C387328 ,U$1 U$2 U$3 U$4 U$5 U$6 U$7 U$8 U$9 U$10 U$11 U$12 U$13 U$14 U$15 U$16,SMD-3225_4P,
LED 0603,L1 L2 L3 L4 L5 L6 L7 L8 L9 L10 L11 L12 L13 L14 L15 L16 L17 L18 L19 L20 L21 L22 L23 L24 L25 L26 L27 L28 L29 L30 L31 L32 L33 L34 L35 L36 L37 L38 L39 L40 L41 L42 L43 L44 L45 L46 L47 L48,CHIP-LED0603,
SN74ALVC08LARGE,AND_IC AND_IC1 AND_IC2 AND_IC3 AND_IC4 AND_IC5 AND_IC6 AND_IC7 AND_IC8 AND_IC9 AND_IC10 AND_IC11 AND_IC12 AND_IC13 AND_IC14 AND_IC15,SN74LVC86ARGYR,
SN74LVC1G132DCKT,NAND_IC NAND_IC1 NAND_IC2 NAND_IC3 NAND_IC4 NAND_IC5 NAND_IC6 NAND_IC7 NAND_IC8 NAND_IC9 NAND_IC10 NAND_IC11 NAND_IC12 NAND_IC13 NAND_IC14 NAND_IC15,SOT65P210X110-5N,
SN74LVC86A,XOR_IC XOR_IC1 XOR_IC2 XOR_IC3 XOR_IC4 XOR_IC5 XOR_IC6 XOR_IC7 XOR_IC8 XOR_IC9 XOR_IC10 XOR_IC11 XOR_IC12 XOR_IC13 XOR_IC14 XOR_IC15,SN74LVC86ARGYR,
XF2J-1824-12,J1 J2 J3 J4 J5 J6 J7 J8 J9 J10 J11 J12 J13 J14 J15 J16 J17 J18 J19 J20 J21 J22 J23 J24 J25 J26 J27 J28 J29 J30 J31 J32,XF2J-1824-12,

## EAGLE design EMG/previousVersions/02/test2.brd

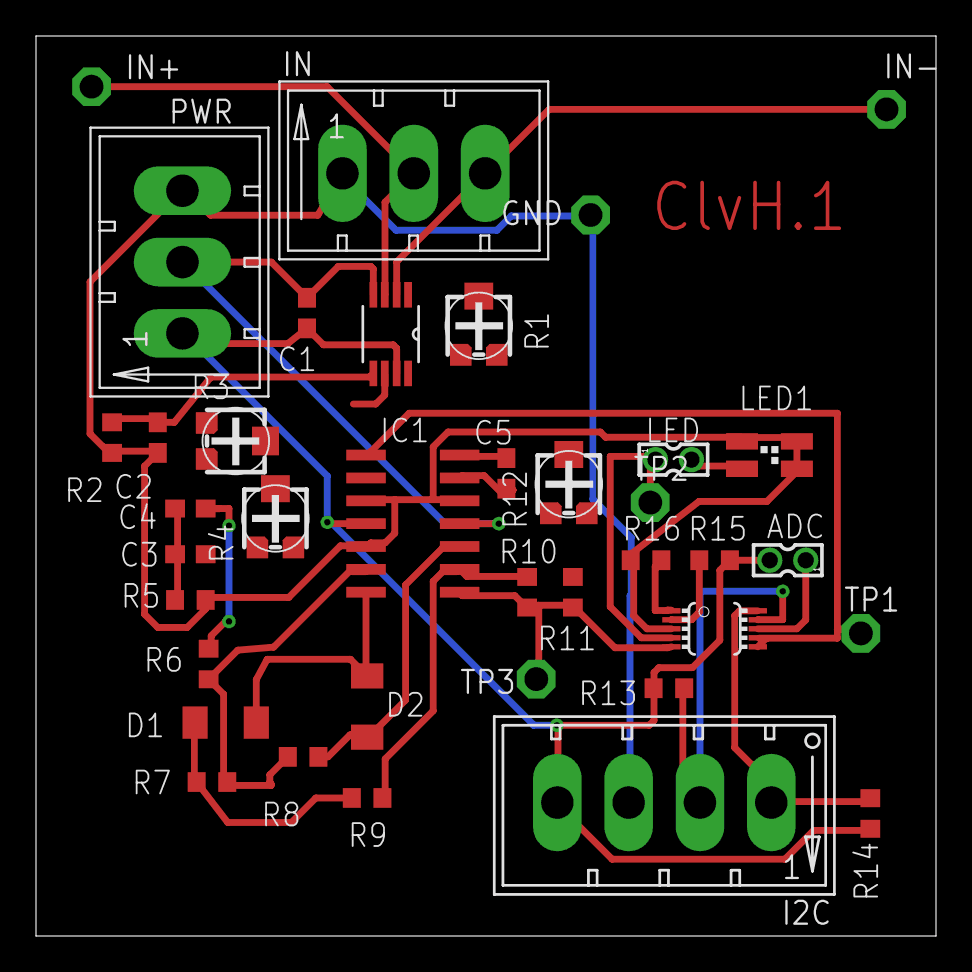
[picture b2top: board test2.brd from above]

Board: 2 copper layers, 50.0 x 50.0 mm, 38 parts (0 on the bottom side), 26 nets.

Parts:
ADC: 332-02
C1, C3, C4, C5: 0.1nF; C0603
C2: 1nF; C0603
D1, D2: SOD80
GND: PTR1PAD1-13; P1-13
I2C: MT6-4Y
IC1: LMV324M; SO14
IN: MT6-3
IN+: PTR1PAD1-13; P1-13
IN-: PTR1PAD1-13; P1-13
LED: 332-02
LED1: P-LCC-4-3
PRECI_AMP: INA326EA/250; SOP65P490X110-8N
PWR: MT6-3
R1, R3, R4, R12: RTRIM4G/J
R2, R5, R6, R7, R8, R9, R10, R11, R13, R14, R15, R16: 100k; R0603
TP1, TP2, TP3: PTR1PAD1-13; P1-13
U$1: ADS1015IDGT; MSOP10_0.5

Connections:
GNDA: C2.1, GND.TP, I2C.3, IC1.3, IC1.5, IC1.12, IN.1, LED1.1, LED1.3, LED1.4, PWR.3, R2.1, R5.2, R16.2, U$1.3
unnamed: PRECI_AMP.1, R1.2
unnamed: PRECI_AMP.8, R1.1
unnamed: IN.2, IN+.TP, PRECI_AMP.3
unnamed: C2.2, PRECI_AMP.5, R2.2
unnamed: IN.3, IN-.TP, PRECI_AMP.2
unnamed: C3.2, C4.2, R3.1, R5.1
unnamed: C3.1, IC1.2, R4.3
unnamed: C4.1, IC1.1, R4.2, R6.1, TP1.TP, U$1.6, U$1.7
unnamed: PRECI_AMP.6, R3.2
unnamed: IC1.6, R6.2, R7.1, R8.1
unnamed: D2.1, IC1.10, R8.2
unnamed: IC1.9, R9.2, R10.1
unnamed: D1.1, D2.2, IC1.7
unnamed: D1.2, R7.2, R9.1
unnamed: IC1.8, R10.2, R11.1, TP3.TP, U$1.5
unnamed: C5.2, IC1.13, R11.2, R12.3
unnamed: I2C.2, R13.1, U$1.9
unnamed: R16.1, U$1.1
unnamed: R15.2, U$1.2
unnamed: LED.2, LED1.2
unnamed: I2C.1, R14.2, U$1.10
unnamed: C5.1, IC1.14, LED.1, R12.2, TP2.TP, U$1.4
V+: ADC.2, C1.1, I2C.4, IC1.4, PRECI_AMP.7, PWR.1, R13.2, R14.1, R15.1
V-: C1.2, IC1.11, PRECI_AMP.4, PWR.2
VDD: ADC.1, U$1.8

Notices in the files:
parts and their libraries:
SparkFun-Aesthetics: Licensing: Creative Commons ShareAlike 4.0 International - https://creativecommons.org/licenses/by-sa/4.0
